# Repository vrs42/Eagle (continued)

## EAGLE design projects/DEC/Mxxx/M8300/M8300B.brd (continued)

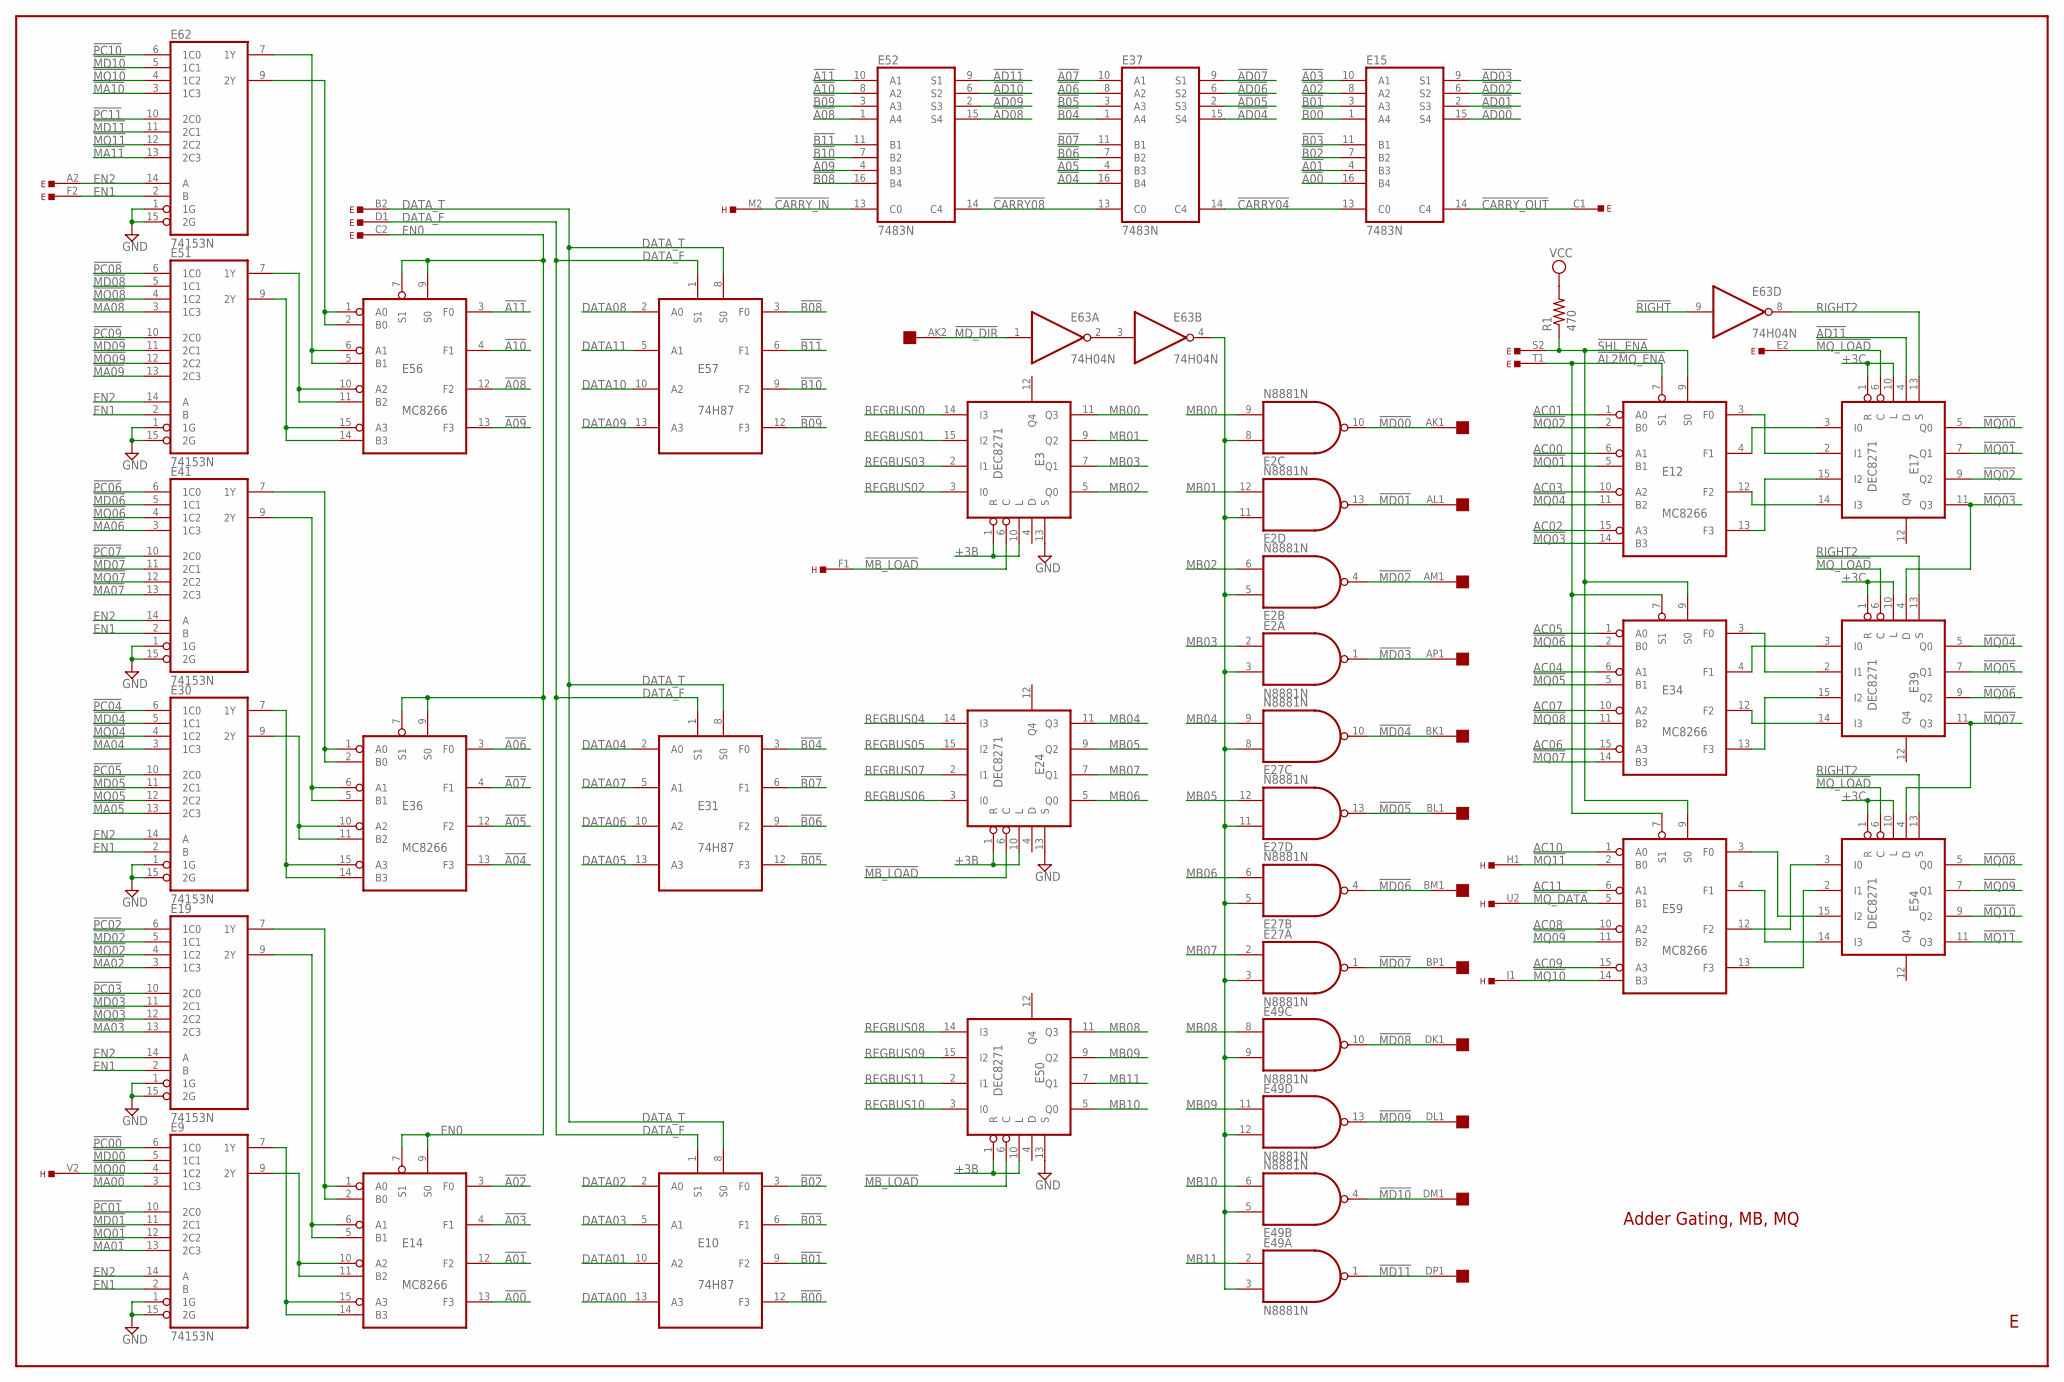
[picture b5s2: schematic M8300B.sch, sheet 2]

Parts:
E: EDGE-TOP; EDGE-CON2
E2, E27, E49: N8881N; DIL14
E3, E17, E24, E39, E50, E54: DEC8271; DIL16
E9, E19, E30, E41, E51, E62: 74153N; DIL16
E10, E31, E57: 74H87; DIL14
E12, E14, E34, E36, E56, E59: MC8266; DIL16
E15, E37, E52: 7483N; DIL16
E63: 74H04N; DIL14
H: EDGE-TOP; EDGE-CON2
R1: 470; 0207/10
U$2: QUAD; EDGE-CON8

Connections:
!A00: E14.13 (F3), E15.16 (B4)
!A01: E14.12 (F2), E15.4 (B3)
!A02: E14.3 (F0), E15.8 (A2)
!A03: E14.4 (F1), E15.10 (A1)
!A04: E36.13 (F3), E37.16 (B4)
!A05: E36.12 (F2), E37.4 (B3)
!A06: E36.3 (F0), E37.8 (A2)
!A07: E36.4 (F1), E37.10 (A1)
!A08: E52.1 (A4), E56.12 (F2)
!A09: E52.4 (B3), E56.13 (F3)
!A10: E52.8 (A2), E56.4 (F1)
!A11: E52.10 (A1), E56.3 (F0)
!AD00: E15.15 (S4); also elsewhere on the board
!AD01: E15.2 (S3); also elsewhere on the board
!AD02: E15.6 (S2); also elsewhere on the board
!AD03: E15.9 (S1); also elsewhere on the board
!AD04: E37.15 (S4); also elsewhere on the board
!AD05: E37.2 (S3); also elsewhere on the board
!AD06: E37.6 (S2); also elsewhere on the board
!AD07: E37.9 (S1); also elsewhere on the board
!AD08: E52.15 (S4); also elsewhere on the board
!AD09: E52.2 (S3); also elsewhere on the board
!AD10: E52.6 (S2); also elsewhere on the board
!AD11: E17.4 (D), E52.9 (S1); also elsewhere on the board
!AL2MQ_ENA: E.T1, E12.7 (S1), E34.7 (S1), E59.7 (S1)
!B00: E10.12 (F3), E15.1 (A4)
!B01: E10.9 (F2), E15.3 (A3)
!B02: E10.3 (F0), E15.7 (B2)
!B03: E10.6 (F1), E15.11 (B1)
!B04: E31.3 (F0), E37.1 (A4)
!B05: E31.12 (F3), E37.3 (A3)
!B06: E31.9 (F2), E37.7 (B2)
!B07: E31.6 (F1), E37.11 (B1)
!B08: E52.16 (B4), E57.3 (F0)
!B09: E52.3 (A3), E57.12 (F3)
!B10: E52.7 (B2), E57.9 (F2)
!B11: E52.11 (B1), E57.6 (F1)
!CARRY04: E15.13 (C0), E37.14 (C4)
!CARRY08: E37.13 (C0), E52.14 (C4)
!CARRY_IN: E52.13 (C0), H.M2
!CARRY_OUT: E.C1, E15.14 (C4)
!MA00: E9.3 (1C3); also elsewhere on the board
!MA01: E9.13 (2C3); also elsewhere on the board
!MA02: E19.3 (1C3); also elsewhere on the board
!MA03: E19.13 (2C3); also elsewhere on the board
!MA04: E30.3 (1C3); also elsewhere on the board
!MA05: E30.13 (2C3); also elsewhere on the board
!MA06: E41.3 (1C3); also elsewhere on the board
!MA07: E41.13 (2C3); also elsewhere on the board
!MA08: E51.3 (1C3); also elsewhere on the board
!MA09: E51.13 (2C3); also elsewhere on the board
!MA10: E62.3 (1C3); also elsewhere on the board
!MA11: E62.13 (2C3); also elsewhere on the board
!MB_LOAD: E3.6 (C), E24.6 (C), E50.6 (C), H.F1
!MD00: E2.10 (O), E9.5 (1C1), U$2.AK1
!MD01: E2.13 (O), E9.11 (2C1), U$2.AL1
!MD02: E2.4 (O), E19.5 (1C1), U$2.AM1
!MD03: E2.1 (O), E19.11 (2C1), U$2.AP1
!MD04: E27.10 (O), E30.5 (1C1), U$2.BK1
!MD05: E27.13 (O), E30.11 (2C1), U$2.BL1; also elsewhere on the board
!MD06: E27.4 (O), E41.5 (1C1), U$2.BM1; also elsewhere on the board
!MD07: E27.1 (O), E41.11 (2C1), U$2.BP1; also elsewhere on the board
!MD08: E49.10 (O), E51.5 (1C1), U$2.DK1; also elsewhere on the board
!MD09: E49.13 (O), E51.11 (2C1), U$2.DL1; also elsewhere on the board
!MD10: E49.4 (O), E62.5 (1C1), U$2.DM1; also elsewhere on the board
!MD11: E49.1 (O), E62.11 (2C1), U$2.DP1; also elsewhere on the board
!MD_DIR: E63.1 (I), U$2.AK2
!MQ00: E9.4 (1C2), E17.5 (Q0), H.V2; also elsewhere on the board
!MQ01: E9.12 (2C2), E12.5 (B1), E17.7 (Q1); also elsewhere on the board
!MQ02: E12.2 (B0), E17.9 (Q2), E19.4 (1C2); also elsewhere on the board
!MQ03: E12.14 (B3), E17.11 (Q3), E19.12 (2C2), E39.4 (D); also elsewhere on the board
!MQ04: E12.11 (B2), E30.4 (1C2), E39.5 (Q0); also elsewhere on the board
!MQ05: E30.12 (2C2), E34.5 (B1), E39.7 (Q1); also elsewhere on the board
!MQ06: E34.2 (B0), E39.9 (Q2), E41.4 (1C2); also elsewhere on the board
!MQ07: E34.14 (B3), E39.11 (Q3), E41.12 (2C2), E54.4 (D); also elsewhere on the board
!MQ08: E34.11 (B2), E51.4 (1C2), E54.5 (Q0); also elsewhere on the board
!MQ09: E51.12 (2C2), E54.7 (Q1), E59.11 (B2); also elsewhere on the board
!MQ10: E54.9 (Q2), E59.14 (B3), E62.4 (1C2), H.J1; also elsewhere on the board
!MQ11: E54.11 (Q3), E59.2 (B0), E62.12 (2C2), H.H1; also elsewhere on the board
!MQ_DATA: E59.5 (B1), H.U2
!MQ_LOAD: E.E2, E17.6 (C), E39.6 (C), E54.6 (C)
!PC00: E9.6 (1C0); also elsewhere on the board
!PC01: E9.10 (2C0); also elsewhere on the board
!PC02: E19.6 (1C0); also elsewhere on the board
!PC03: E19.10 (2C0); also elsewhere on the board
!PC04: E30.6 (1C0); also elsewhere on the board
!PC05: E30.10 (2C0); also elsewhere on the board
!PC06: E41.6 (1C0); also elsewhere on the board
!PC07: E41.10 (2C0); also elsewhere on the board
!PC08: E51.6 (1C0); also elsewhere on the board
!PC09: E51.10 (2C0); also elsewhere on the board
!PC10: E62.6 (1C0); also elsewhere on the board
!PC11: E62.10 (2C0); also elsewhere on the board
!RIGHT: E63.9 (I); also elsewhere on the board
!SHL_ENA: E.S2, E12.9 (S0), E34.9 (S0), E59.9 (S0), R1.1
+3B: E3.1 (R), E3.10 (L), E24.1 (R), E24.10 (L), E50.1 (R), E50.10 (L); also elsewhere on the board
+3C: E17.1 (R), E17.10 (L), E39.1 (R), E39.10 (L), E54.1 (R), E54.10 (L); also elsewhere on the board
AC00: E12.6 (A1); also elsewhere on the board
AC01: E12.1 (A0); also elsewhere on the board
AC02: E12.15 (A3); also elsewhere on the board
AC03: E12.10 (A2); also elsewhere on the board
AC04: E34.6 (A1); also elsewhere on the board
AC05: E34.1 (A0); also elsewhere on the board
AC06: E34.15 (A3); also elsewhere on the board
AC07: E34.10 (A2); also elsewhere on the board
AC08: E59.10 (A2); also elsewhere on the board
AC09: E59.15 (A3); also elsewhere on the board
AC10: E59.1 (A0); also elsewhere on the board
AC11: E59.6 (A1); also elsewhere on the board
DATA00: E10.13 (A3); also elsewhere on the board
DATA01: E10.10 (A2); also elsewhere on the board
DATA02: E10.2 (A0); also elsewhere on the board
DATA03: E10.5 (A1); also elsewhere on the board
DATA04: E31.2 (A0); also elsewhere on the board
DATA05: E31.13 (A3); also elsewhere on the board
DATA06: E31.10 (A2); also elsewhere on the board
DATA07: E31.5 (A1); also elsewhere on the board
DATA08: E57.2 (A0); also elsewhere on the board
DATA09: E57.13 (A3); also elsewhere on the board
DATA10: E57.10 (A2); also elsewhere on the board
DATA11: E57.5 (A1); also elsewhere on the board
DATA_F: E.D1, E10.1 (S1), E31.1 (S1), E57.1 (S1)
DATA_T: E.B2, E10.8 (S0), E31.8 (S0), E57.8 (S0)
EN0: E.C2, E14.7 (S1), E14.9 (S0), E36.7 (S1), E36.9 (S0), E56.7 (S1), E56.9 (S0)
EN1: E.F2, E9.2 (B), E19.2 (B), E30.2 (B), E41.2 (B), E51.2 (B), E62.2 (B)
EN2: E.A2, E9.14 (A), E19.14 (A), E30.14 (A), E41.14 (A), E51.14 (A), E62.14 (A)
GND: E2.7 (GND), E3.8 (GND), E3.13 (S), E9.1 (1G), E9.8 (GND), E9.15 (2G), E10.7 (GND), E12.8 (GND), E14.8 (GND), E15.12 (GND), E17.8 (GND), E19.1 (1G), E19.8 (GND), E19.15 (2G), E24.8 (GND), E24.13 (S), E27.7 (GND), E30.1 (1G), E30.8 (GND), E30.15 (2G), E31.7 (GND), E34.8 (GND), E36.8 (GND), E37.12 (GND), E39.8 (GND), E41.1 (1G), E41.8 (GND), E41.15 (2G), E49.7 (GND), E50.8 (GND), E50.13 (S), E51.1 (1G), E51.8 (GND), E51.15 (2G), E52.12 (GND), E54.8 (GND), E56.8 (GND), E57.7 (GND), E59.8 (GND), E62.1 (1G), E62.8 (GND), E62.15 (2G), E63.7 (GND); also elsewhere on the board
MB00: E2.9 (I1), E3.11 (Q3); also elsewhere on the board
MB01: E2.12 (I1), E3.9 (Q2); also elsewhere on the board
MB02: E2.6 (I1), E3.5 (Q0); also elsewhere on the board
MB03: E2.2 (I0), E3.7 (Q1); also elsewhere on the board
MB04: E24.11 (Q3), E27.9 (I1); also elsewhere on the board
MB05: E24.9 (Q2), E27.12 (I1); also elsewhere on the board
MB06: E24.5 (Q0), E27.6 (I1); also elsewhere on the board
MB07: E24.7 (Q1), E27.2 (I0); also elsewhere on the board
MB08: E49.8 (I0), E50.11 (Q3); also elsewhere on the board
MB09: E49.11 (I0), E50.9 (Q2); also elsewhere on the board
MB10: E49.6 (I1), E50.5 (Q0); also elsewhere on the board
MB11: E49.2 (I0), E50.7 (Q1); also elsewhere on the board
unnamed: E12.3 (F0), E17.2 (I1)
unnamed: E34.12 (F2), E39.14 (I3)
unnamed: E34.4 (F1), E39.3 (I0)
unnamed: E63.2 (O), E63.3 (I)
unnamed: E12.4 (F1), E17.3 (I0)
unnamed: E54.15 (I2), E59.3 (F0)
unnamed: E9.9 (2Y), E14.10 (A2), E14.11 (B2)
unnamed: E9.7 (1Y), E14.14 (B3), E14.15 (A3)
unnamed: E51.7 (1Y), E56.10 (A2), E56.11 (B2)
unnamed: E34.3 (F0), E39.2 (I1)
unnamed: E2.3 (I1), E2.5 (I0), E2.8 (I0), E2.11 (I0), E27.3 (I1), E27.5 (I0), E27.8 (I0), E27.11 (I0), E49.3 (I1), E49.5 (I0), E49.9 (I1), E49.12 (I1), E63.4 (O)
unnamed: E14.5 (B1), E14.6 (A1), E19.9 (2Y)
unnamed: E34.13 (F3), E39.15 (I2)
unnamed: E54.2 (I1), E59.13 (F3)
unnamed: E54.14 (I3), E59.4 (F1)
unnamed: E14.1 (A0), E14.2 (B0), E19.7 (1Y)
unnamed: E54.3 (I0), E59.12 (F2)
unnamed: E12.12 (F2), E17.14 (I3)
unnamed: E12.13 (F3), E17.15 (I2)
unnamed: E30.7 (1Y), E36.14 (B3), E36.15 (A3)
unnamed: E30.9 (2Y), E36.10 (A2), E36.11 (B2)
unnamed: E36.5 (B1), E36.6 (A1), E41.9 (2Y)
unnamed: E36.1 (A0), E36.2 (B0), E41.7 (1Y)
unnamed: E51.9 (2Y), E56.14 (B3), E56.15 (A3)
unnamed: E56.5 (B1), E56.6 (A1), E62.7 (1Y)
unnamed: E56.1 (A0), E56.2 (B0), E62.9 (2Y)
REGBUS00: E3.14 (I3); also elsewhere on the board
REGBUS01: E3.15 (I2); also elsewhere on the board
REGBUS02: E3.3 (I0); also elsewhere on the board
REGBUS03: E3.2 (I1); also elsewhere on the board
REGBUS04: E24.14 (I3); also elsewhere on the board
REGBUS05: E24.15 (I2); also elsewhere on the board
REGBUS06: E24.3 (I0); also elsewhere on the board
REGBUS07: E24.2 (I1); also elsewhere on the board
REGBUS08: E50.14 (I3); also elsewhere on the board
REGBUS09: E50.15 (I2); also elsewhere on the board
REGBUS10: E50.3 (I0); also elsewhere on the board
REGBUS11: E50.2 (I1); also elsewhere on the board
RIGHT2: E17.13 (S), E39.13 (S), E54.13 (S), E63.8 (O)
VCC: E2.14 (VCC), E3.16 (VCC), E9.16 (VCC), E10.14 (VCC), E12.16 (VCC), E14.16 (VCC), E15.5 (VCC), E17.16 (VCC), E19.16 (VCC), E24.16 (VCC), E27.14 (VCC), E30.16 (VCC), E31.14 (VCC), E34.16 (VCC), E36.16 (VCC), E37.5 (VCC), E39.16 (VCC), E41.16 (VCC), E49.14 (VCC), E50.16 (VCC), E51.16 (VCC), E52.5 (VCC), E54.16 (VCC), E56.16 (VCC), E57.14 (VCC), E59.16 (VCC), E62.16 (VCC), E63.14 (VCC), R1.2; also elsewhere on the board

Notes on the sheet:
Adder Gating, MB, MQ

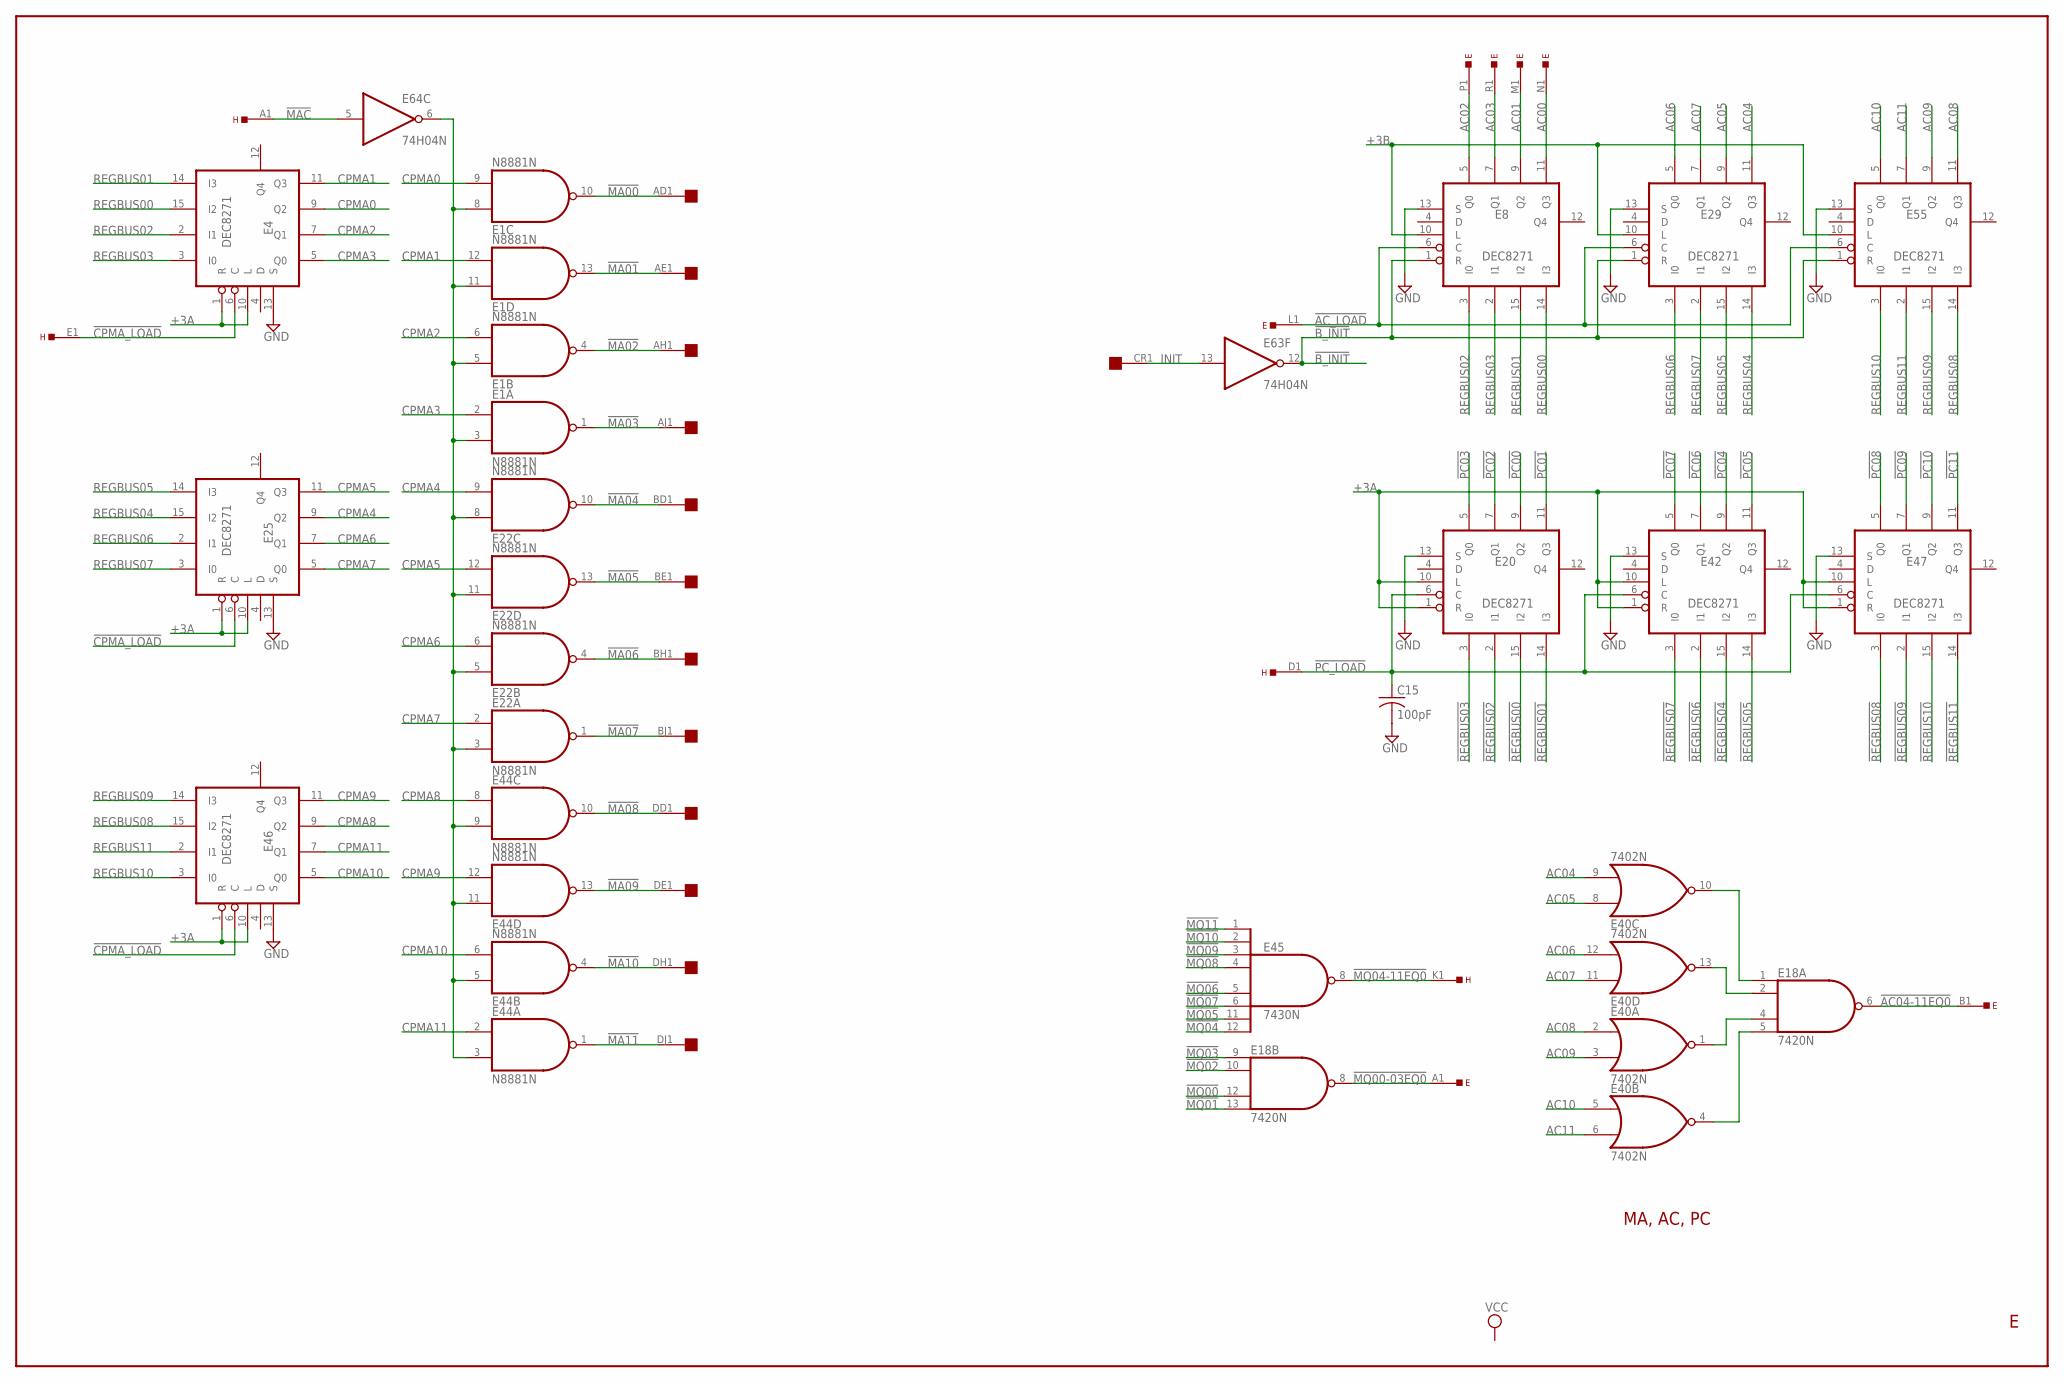
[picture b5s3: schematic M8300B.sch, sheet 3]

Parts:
C15: 100pF; C063-025X075
E: EDGE-TOP; EDGE-CON2
E1, E22, E44: N8881N; DIL14
E4, E8, E20, E25, E29, E42, E46, E47, E55: DEC8271; DIL16
E18: 7420N; DIL14
E40: 7402N; DIL14
E45: 7430N; DIL14
E63, E64: 74H04N; DIL14
H: EDGE-TOP; EDGE-CON2
U$2: QUAD; EDGE-CON8

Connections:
!AC04-11EQ0: E.B1, E18.6 (O)
!AC_LOAD: E.L1, E8.6 (C), E29.6 (C), E55.6 (C)
!B_INIT: E8.1 (R), E29.1 (R), E55.1 (R), E63.12 (O)
!CPMA_LOAD: E4.6 (C), E25.6 (C), E46.6 (C), H.E1
!MA00: E1.10 (O), U$2.AD1; also elsewhere on the board
!MA01: E1.13 (O), U$2.AE1; also elsewhere on the board
!MA02: E1.4 (O), U$2.AH1; also elsewhere on the board
!MA03: E1.1 (O), U$2.AJ1; also elsewhere on the board
!MA04: E22.10 (O), U$2.BD1; also elsewhere on the board
!MA05: E22.13 (O), U$2.BE1; also elsewhere on the board
!MA06: E22.4 (O), U$2.BH1; also elsewhere on the board
!MA07: E22.1 (O), U$2.BJ1; also elsewhere on the board
!MA08: E44.10 (O), U$2.DD1; also elsewhere on the board
!MA09: E44.13 (O), U$2.DE1; also elsewhere on the board
!MA10: E44.4 (O), U$2.DH1; also elsewhere on the board
!MA11: E44.1 (O), U$2.DJ1; also elsewhere on the board
!MAC: E64.5 (I), H.A1
!MQ00: E18.12 (I2); also elsewhere on the board
!MQ00-03EQ0: E.A1, E18.8 (O)
!MQ01: E18.13 (I3); also elsewhere on the board
!MQ02: E18.10 (I1); also elsewhere on the board
!MQ03: E18.9 (I0); also elsewhere on the board
!MQ04: E45.12 (I7); also elsewhere on the board
!MQ04-11EQ0: E45.8 (O), H.K1
!MQ05: E45.11 (I6); also elsewhere on the board
!MQ06: E45.5 (I4); also elsewhere on the board
!MQ07: E45.6 (I5); also elsewhere on the board
!MQ08: E45.4 (I3); also elsewhere on the board
!MQ09: E45.3 (I2); also elsewhere on the board
!MQ10: E45.2 (I1); also elsewhere on the board
!MQ11: E45.1 (I0); also elsewhere on the board
!PC00: E20.9 (Q2); also elsewhere on the board
!PC01: E20.11 (Q3); also elsewhere on the board
!PC02: E20.7 (Q1); also elsewhere on the board
!PC03: E20.5 (Q0); also elsewhere on the board
!PC04: E42.9 (Q2); also elsewhere on the board
!PC05: E42.11 (Q3); also elsewhere on the board
!PC06: E42.7 (Q1); also elsewhere on the board
!PC07: E42.5 (Q0); also elsewhere on the board
!PC08: E47.5 (Q0); also elsewhere on the board
!PC09: E47.7 (Q1); also elsewhere on the board
!PC10: E47.9 (Q2); also elsewhere on the board
!PC11: E47.11 (Q3); also elsewhere on the board
!PC_LOAD: C15.1, E20.6 (C), E42.6 (C), E47.6 (C), H.D1
!REGBUS00: E20.15 (I2); also elsewhere on the board
!REGBUS01: E20.14 (I3); also elsewhere on the board
!REGBUS02: E20.2 (I1); also elsewhere on the board
!REGBUS03: E20.3 (I0); also elsewhere on the board
!REGBUS04: E42.15 (I2); also elsewhere on the board
!REGBUS05: E42.14 (I3); also elsewhere on the board
!REGBUS06: E42.2 (I1); also elsewhere on the board
!REGBUS07: E42.3 (I0); also elsewhere on the board
!REGBUS08: E47.3 (I0); also elsewhere on the board
!REGBUS09: E47.2 (I1); also elsewhere on the board
!REGBUS10: E47.15 (I2); also elsewhere on the board
!REGBUS11: E47.14 (I3); also elsewhere on the board
+3A: E4.1 (R), E4.10 (L), E20.1 (R), E20.10 (L), E25.1 (R), E25.10 (L), E42.1 (R), E42.10 (L), E46.1 (R), E46.10 (L), E47.1 (R), E47.10 (L); also elsewhere on the board
+3B: E8.10 (L), E29.10 (L), E55.10 (L); also elsewhere on the board
AC00: E.N1, E8.11 (Q3); also elsewhere on the board
AC01: E.M1, E8.9 (Q2); also elsewhere on the board
AC02: E.P1, E8.5 (Q0); also elsewhere on the board
AC03: E.R1, E8.7 (Q1); also elsewhere on the board
AC04: E29.11 (Q3), E40.9 (I1); also elsewhere on the board
AC05: E29.9 (Q2), E40.8 (I0); also elsewhere on the board
AC06: E29.5 (Q0), E40.12 (I1); also elsewhere on the board
AC07: E29.7 (Q1), E40.11 (I0); also elsewhere on the board
AC08: E40.2 (I0), E55.11 (Q3); also elsewhere on the board
AC09: E40.3 (I1), E55.9 (Q2); also elsewhere on the board
AC10: E40.5 (I0), E55.5 (Q0); also elsewhere on the board
AC11: E40.6 (I1), E55.7 (Q1); also elsewhere on the board
CPMA0: E1.9 (I1), E4.9 (Q2)
CPMA1: E1.12 (I1), E4.11 (Q3)
CPMA2: E1.6 (I1), E4.7 (Q1)
CPMA3: E1.2 (I0), E4.5 (Q0)
CPMA4: E22.9 (I1), E25.9 (Q2)
CPMA5: E22.12 (I1), E25.11 (Q3)
CPMA6: E22.6 (I1), E25.7 (Q1)
CPMA7: E22.2 (I0), E25.5 (Q0)
CPMA8: E44.8 (I0), E46.9 (Q2)
CPMA9: E44.12 (I1), E46.11 (Q3)
CPMA10: E44.6 (I1), E46.5 (Q0)
CPMA11: E44.2 (I0), E46.7 (Q1)
GND: C15.2, E1.7 (GND), E4.8 (GND), E4.13 (S), E8.8 (GND), E8.13 (S), E18.7 (GND), E20.8 (GND), E20.13 (S), E22.7 (GND), E25.8 (GND), E25.13 (S), E29.8 (GND), E29.13 (S), E40.7 (GND), E42.8 (GND), E42.13 (S), E44.7 (GND), E45.7 (GND), E46.8 (GND), E46.13 (S), E47.8 (GND), E47.13 (S), E55.8 (GND), E55.13 (S), E63.7 (GND), E64.7 (GND); also elsewhere on the board
INIT: E63.13 (I), U$2.CR1
unnamed: E1.3 (I1), E1.5 (I0), E1.8 (I0), E1.11 (I0), E22.3 (I1), E22.5 (I0), E22.8 (I0), E22.11 (I0), E44.3 (I1), E44.5 (I0), E44.9 (I1), E44.11 (I0), E64.6 (O)
unnamed: E18.4 (I2), E40.1 (O)
unnamed: E18.2 (I1), E40.13 (O)
unnamed: E18.5 (I3), E40.4 (O)
unnamed: E18.1 (I0), E40.10 (O)
REGBUS00: E4.15 (I2), E8.14 (I3); also elsewhere on the board
REGBUS01: E4.14 (I3), E8.15 (I2); also elsewhere on the board
REGBUS02: E4.2 (I1), E8.3 (I0); also elsewhere on the board
REGBUS03: E4.3 (I0), E8.2 (I1); also elsewhere on the board
REGBUS04: E25.15 (I2), E29.14 (I3); also elsewhere on the board
REGBUS05: E25.14 (I3), E29.15 (I2); also elsewhere on the board
REGBUS06: E25.2 (I1), E29.3 (I0); also elsewhere on the board
REGBUS07: E25.3 (I0), E29.2 (I1); also elsewhere on the board
REGBUS08: E46.15 (I2), E55.14 (I3); also elsewhere on the board
REGBUS09: E46.14 (I3), E55.15 (I2); also elsewhere on the board
REGBUS10: E46.3 (I0), E55.3 (I0); also elsewhere on the board
REGBUS11: E46.2 (I1), E55.2 (I1); also elsewhere on the board
VCC: E1.14 (VCC), E4.16 (VCC), E8.16 (VCC), E18.14 (VCC), E20.16 (VCC), E22.14 (VCC), E25.16 (VCC), E29.16 (VCC), E40.14 (VCC), E42.16 (VCC), E44.14 (VCC), E45.14 (VCC), E46.16 (VCC), E47.16 (VCC), E55.16 (VCC), E63.14 (VCC), E64.14 (VCC); also elsewhere on the board

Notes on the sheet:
MA, AC, PC

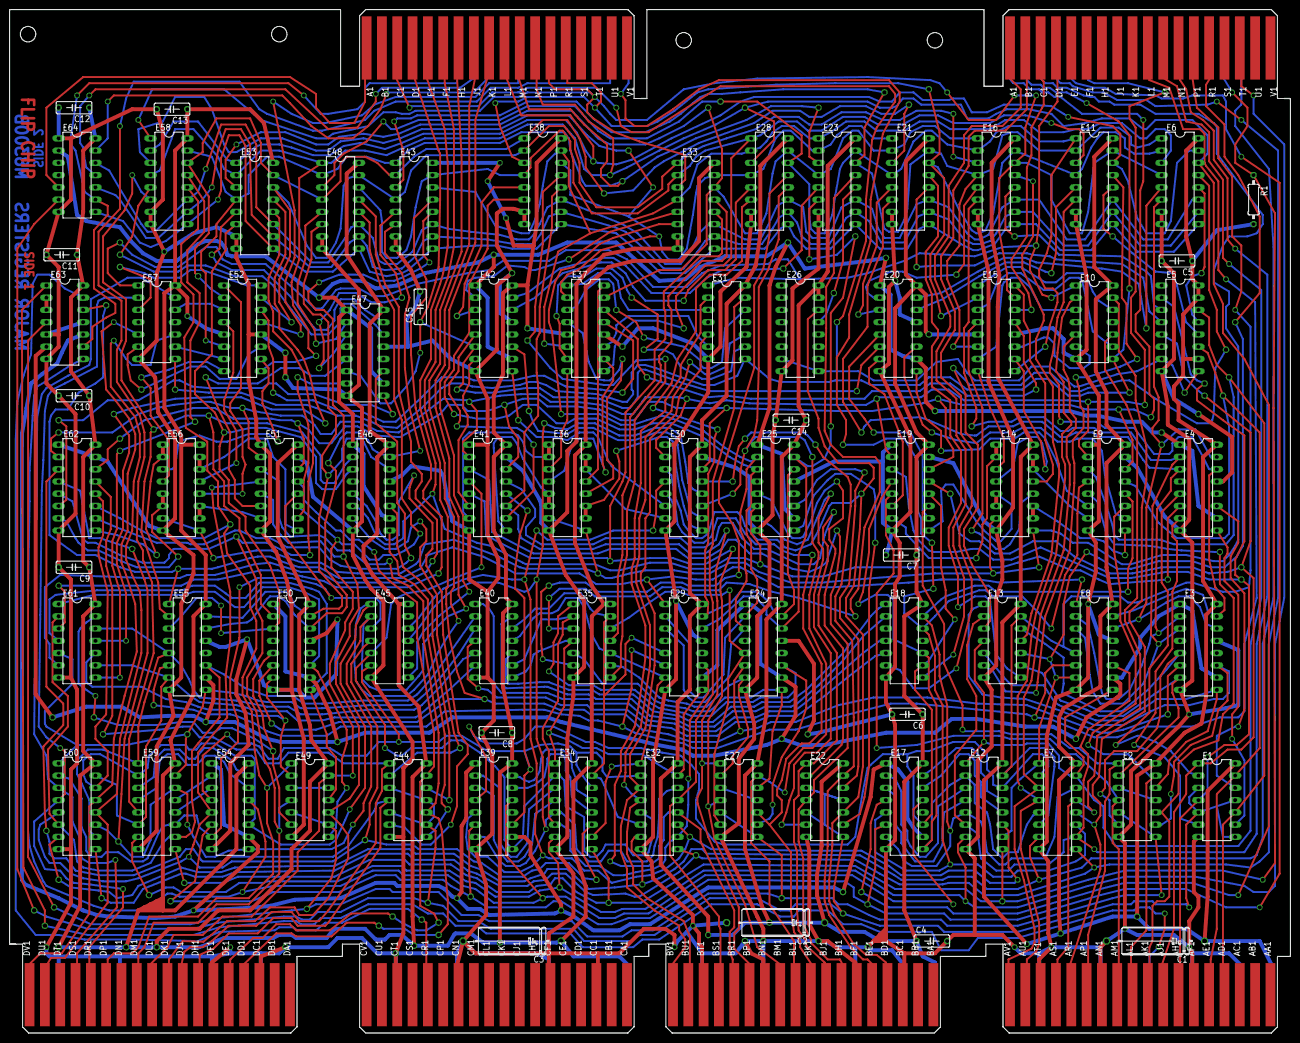
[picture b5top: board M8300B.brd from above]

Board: 3 copper layers, 265.4 x 212.1 mm, 83 parts (0 on the bottom side), 244 nets.
